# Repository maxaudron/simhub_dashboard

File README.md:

# SIMHUB Dashboard

## Hardware Requirements
- SK6812MINI LEDs
- Arduino
- [Vocore 5" Screen](https://vocore.io/)

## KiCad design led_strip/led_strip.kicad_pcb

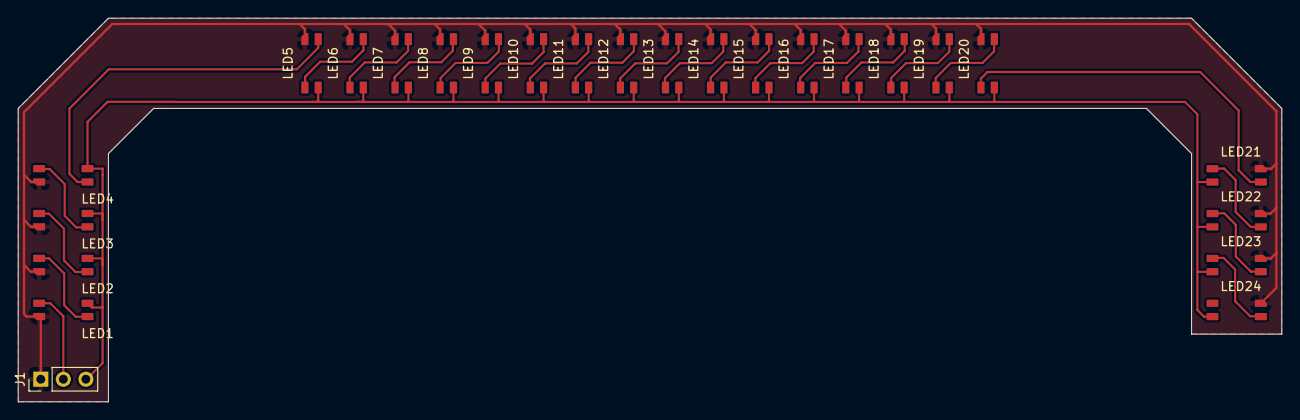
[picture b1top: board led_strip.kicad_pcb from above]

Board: 2 copper layers, 142.2 x 43.2 mm, 25 parts (0 on the bottom side), 26 nets.

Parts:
J1: Conn_01x03_Socket; PinHeader_1x03_P2.54mm_Vertical
LED1, LED2, LED3, LED4, LED5, LED6, LED7, LED8, LED9, LED10, LED11, LED12, LED13, LED14, LED15, LED16, LED17, LED18, LED19, LED20, LED21, LED22, LED23, LED24: MX_SK6812MINI-E; LED_SK6812MINI-R

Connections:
unnamed: J1.1, LED1.4 (VSS), LED2.4 (VSS), LED3.4 (VSS), LED4.4 (VSS), LED5.4 (VSS), LED6.4 (VSS), LED7.4 (VSS), LED8.4 (VSS), LED9.4 (VSS), LED10.4 (VSS), LED11.4 (VSS), LED12.4 (VSS), LED13.4 (VSS), LED14.4 (VSS), LED15.4 (VSS), LED16.4 (VSS), LED17.4 (VSS), LED18.4 (VSS), LED19.4 (VSS), LED20.4 (VSS), LED21.4 (VSS), LED22.4 (VSS), LED23.4 (VSS), LED24.4 (VSS)
unnamed: J1.2, LED1.3 (DIN)
unnamed: J1.3, LED1.1 (VDD), LED2.1 (VDD), LED3.1 (VDD), LED4.1 (VDD), LED5.1 (VDD), LED6.1 (VDD), LED7.1 (VDD), LED8.1 (VDD), LED9.1 (VDD), LED10.1 (VDD), LED11.1 (VDD), LED12.1 (VDD), LED13.1 (VDD), LED14.1 (VDD), LED15.1 (VDD), LED16.1 (VDD), LED17.1 (VDD), LED18.1 (VDD), LED19.1 (VDD), LED20.1 (VDD), LED21.1 (VDD), LED22.1 (VDD), LED23.1 (VDD), LED24.1 (VDD)
unnamed: LED1.2 (DOUT), LED2.3 (DIN)
unnamed: LED2.2 (DOUT), LED3.3 (DIN)
unnamed: LED3.2 (DOUT), LED4.3 (DIN)
unnamed: LED4.2 (DOUT), LED5.3 (DIN)
unnamed: LED5.2 (DOUT), LED6.3 (DIN)
unnamed: LED6.2 (DOUT), LED7.3 (DIN)
unnamed: LED7.2 (DOUT), LED8.3 (DIN)
unnamed: LED8.2 (DOUT), LED9.3 (DIN)
unnamed: LED9.2 (DOUT), LED10.3 (DIN)
unnamed: LED10.2 (DOUT), LED11.3 (DIN)
unnamed: LED11.2 (DOUT), LED12.3 (DIN)
unnamed: LED12.2 (DOUT), LED13.3 (DIN)
unnamed: LED13.2 (DOUT), LED14.3 (DIN)
unnamed: LED14.2 (DOUT), LED15.3 (DIN)
unnamed: LED15.2 (DOUT), LED16.3 (DIN)
unnamed: LED16.2 (DOUT), LED17.3 (DIN)
unnamed: LED17.2 (DOUT), LED18.3 (DIN)
unnamed: LED18.2 (DOUT), LED19.3 (DIN)
unnamed: LED19.2 (DOUT), LED20.3 (DIN)
unnamed: LED20.2 (DOUT), LED21.3 (DIN)
unnamed: LED21.2 (DOUT), LED22.3 (DIN)
unnamed: LED22.2 (DOUT), LED23.3 (DIN)
unnamed: LED23.2 (DOUT), LED24.3 (DIN)

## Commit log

2023-08-15 init
